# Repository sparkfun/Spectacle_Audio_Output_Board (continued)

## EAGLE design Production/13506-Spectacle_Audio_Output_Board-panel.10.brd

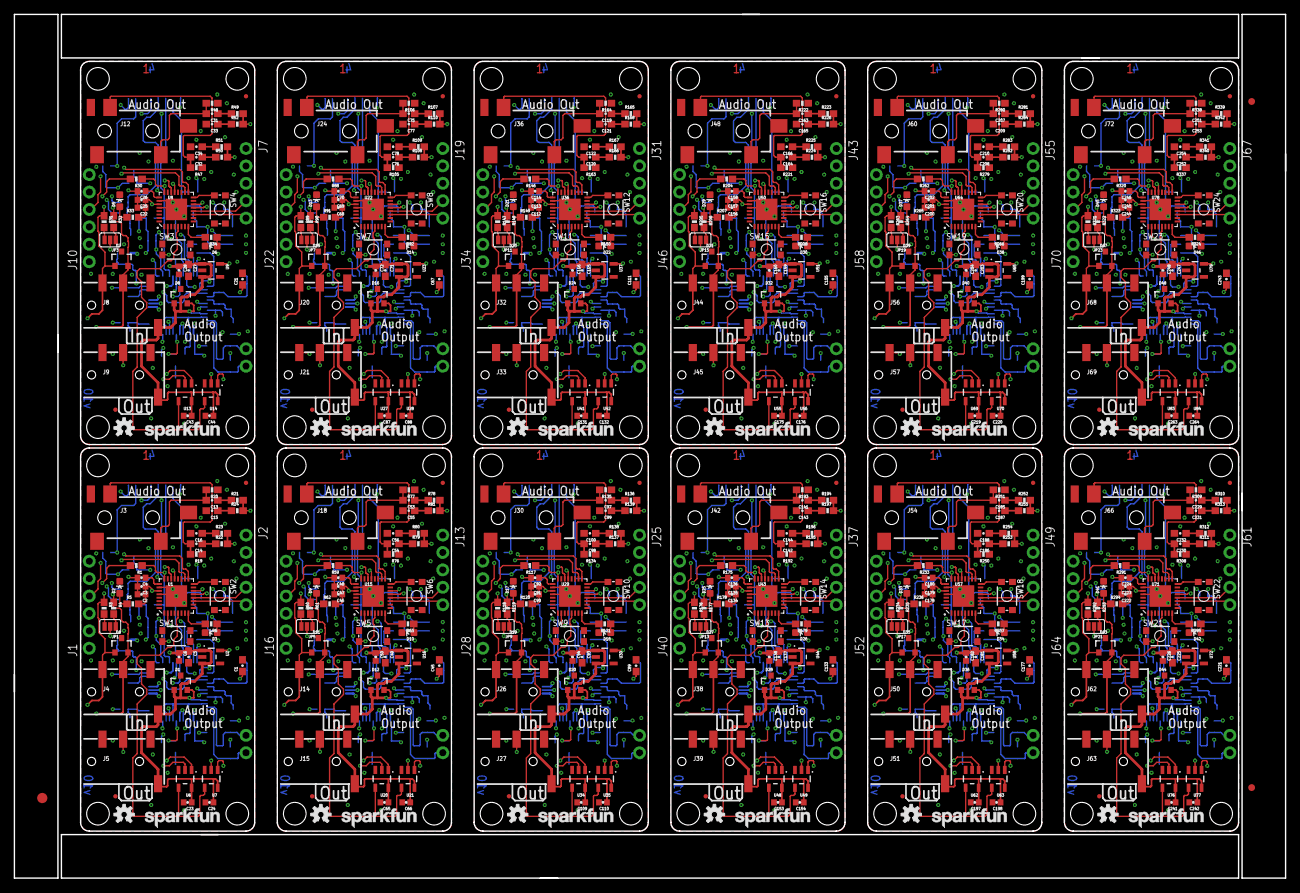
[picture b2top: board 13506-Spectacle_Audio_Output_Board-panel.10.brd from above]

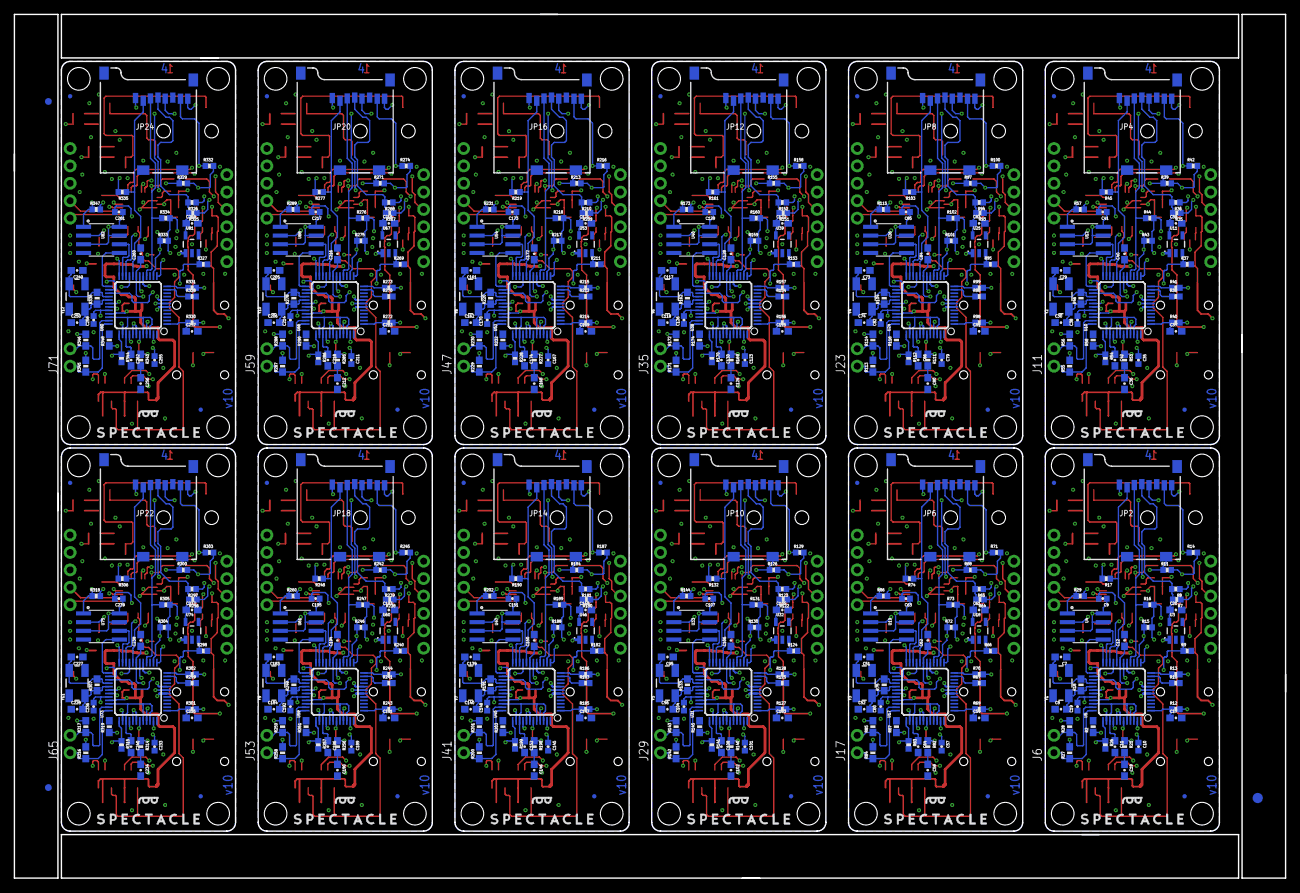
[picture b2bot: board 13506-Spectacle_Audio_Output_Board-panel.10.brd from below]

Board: 4 copper layers, 185.4 x 126.0 mm, 1002 parts (435 on the bottom side), 684 nets.

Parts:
C1, C5, C20, C21, C27, C39, C45, C49, C61, C67, C71, C83, C89, C93, C105, C111, C115, C127, C133, C137, C149, C155, C159, C171, C177, C181, C193, C199, C203, C215, C221, C225, C237, C243, C247, C259: 2.2uF; 0603-CAP
C2, C10, C19, C22, C35, C38, C46, C57, C60, C68, C79, C82, C90, C101, C104, C112, C123, C126, C134, C145, C148, C156, C167, C170, C178, C189, C192, C200, C211, C214, C222, C233, C236, C244, C255, C258: 1.0uF; 0402-CAP
C3, C4, C6, C9, C23, C24, C25, C26, C28, C41, C43, C44, C47, C48, C50, C63, C65, C66, C69, C70, C72, C85, C87, C88, C91, C92, C94, C107, C109, C110, C113, C114, C116, C129, C131, C132, C135, C136, C138, C151, C153, C154, C157, C158, C160, C173, C175, C176, C179, C180, C182, C195, C197, C198, C201, C202, C204, C217, C219, C220, C223, C224, C226, C239, C241, C242, C245, C246, C248, C261, C263, C264: 0.1uF; 0402-CAP
C7, C8, C29, C30, C51, C52, C73, C74, C95, C96, C117, C118, C139, C140, C161, C162, C183, C184, C205, C206, C227, C228, C249, C250: 22pF; 0603-CAP
C11, C12, C13, C14, C17, C31, C32, C37, C40, C42, C53, C54, C59, C62, C64, C75, C76, C81, C84, C86, C97, C98, C103, C106, C108, C119, C120, C125, C128, C130, C141, C142, C147, C150, C152, C163, C164, C169, C172, C174, C185, C186, C191, C194, C196, C207, C208, C213, C216, C218, C229, C230, C235, C238, C240, C251, C252, C257, C260, C262: 10uF; 0603-CAP
C15, C16, C33, C34, C55, C56, C77, C78, C99, C100, C121, C122, C143, C144, C165, C166, C187, C188, C209, C210, C231, C232, C253, C254: 10nF; 0603-CAP
C18, C36, C58, C80, C102, C124, C146, C168, C190, C212, C234, C256: 47nF; 0603-CAP
D1, D4, D7, D8, D11, D12, D15, D16, D19, D20, D23, D24, D27, D28, D31, D32, D35, D36, D39, D40, D43, D44, D47, D48: PESD1CAN; SOT23-3
D2, D3, D5, D6, D9, D10, D13, D14, D17, D18, D21, D22, D25, D26, D29, D30, D33, D34, D37, D38, D41, D42, D45, D46: RED; LED-0603
E$1, E$2: FIDUCIAL-1.5X3
E$3, E$4, E$7, E$8: FIDUCIAL-1X2
FD1, FD2, FD3, FD4, FD5, FD6, FD7, FD8, FD9, FD10, FD11, FD12, FD13, FD14, FD15, FD16, FD17, FD18, FD19, FD20, FD21, FD22, FD23, FD24, FD25, FD26, FD27, FD28, FD29, FD30, FD31, FD32, FD33, FD34, FD35, FD36, FD37, FD38, FD39, FD40, FD41, FD42, FD43, FD44, FD45, FD46, FD47, FD48: FIDUCIALUFIDUCIAL; MICRO-FIDUCIAL
H1, H2, H3, H4, H5, H6, H7, H8, H9, H10, H11, H12, H13, H14, H15, H16, H17, H18, H19, H20, H21, H22, H23, H24, H25, H26, H27, H28, H29, H30, H31, H32, H33, H34, H35, H36, H37, H38, H39, H40, H41, H42, H43, H44, H45, H46, H47, H48: STAND-OFF
J1, J10, J16, J22, J28, J34, J40, J46, J52, J58, J64, J70: 1X06_NO_SILK
J2, J7, J13, J19, J25, J31, J37, J43, J49, J55, J61, J67: 1X05_NO_SILK
J3, J12, J18, J24, J30, J36, J42, J48, J54, J60, J66, J72: AUDIO_JACK_3.5MM_SMD; AUDIO-JACK-3.5MM-SMD
J4, J5, J8, J9, J14, J15, J20, J21, J26, J27, J32, J33, J38, J39, J44, J45, J50, J51, J56, J57, J62, J63, J68, J69: AUDIO_JACK_TRRSSMD_RA; AUDIO_JACK_3.5MM_TRRS_SMD_RA
J6, J11, J17, J23, J29, J35, J41, J47, J53, J59, J65, J71: 1X02_NO_SILK
JP1, JP3, JP5, JP7, JP9, JP11, JP13, JP15, JP17, JP19, JP21, JP23: JUMPER-PAD-3-NC_BY_PASTE; PAD-JUMPER-3-NC_BY_PASTE_YES_SILK_FULL_BOX
JP2, JP4, JP6, JP8, JP10, JP12, JP14, JP16, JP18, JP20, JP22, JP24: USD-SOCKET; MICROSD_1:1
LOGO1, LOGO3, LOGO5, LOGO7, LOGO9, LOGO11, LOGO13, LOGO15, LOGO17, LOGO19, LOGO21, LOGO23: OSHW-LOGOS; OSHW-LOGO-S
LOGO2, LOGO4, LOGO6, LOGO8, LOGO10, LOGO12, LOGO14, LOGO16, LOGO18, LOGO20, LOGO22, LOGO24: SFE_LOGO_NAME.1_INCH; SFE_LOGO_NAME_.1
R1, R19, R20, R30, R47, R48, R59, R76, R77, R88, R105, R106, R117, R134, R135, R146, R163, R164, R175, R192, R193, R204, R221, R222, R233, R250, R251, R262, R279, R280, R291, R308, R309, R320, R337, R338: 10K; 0603-RES
R2, R18, R27, R28, R46, R55, R56, R58, R75, R84, R85, R87, R104, R113, R114, R116, R133, R142, R143, R145, R162, R171, R172, R174, R191, R200, R201, R203, R220, R229, R230, R232, R249, R258, R259, R261, R278, R287, R288, R290, R307, R316, R317, R319, R336, R345, R346, R348: 1M; 0603-RES
R3, R4, R31, R32, R60, R61, R89, R90, R118, R119, R147, R148, R176, R177, R205, R206, R234, R235, R263, R264, R292, R293, R321, R322: 4.7K; 0603-RES
R5, R6, R33, R34, R62, R63, R91, R92, R120, R121, R149, R150, R178, R179, R207, R208, R236, R237, R265, R266, R294, R295, R323, R324: 1K; 0603-RES
R7, R8, R9, R10, R11, R12, R13, R14, R15, R16, R17, R26, R29, R35, R36, R37, R38, R39, R40, R41, R42, R43, R44, R45, R54, R57, R64, R65, R66, R67, R68, R69, R70, R71, R72, R73, R74, R83, R86, R93, R94, R95, R96, R97, R98, R99, R100, R101, R102, R103, R112, R115, R122, R123, R124, R125, R126, R127, R128, R129, R130, R131, R132, R141, R144, R151, R152, R153, R154, R155, R156, R157, R158, R159, R160, R161, R170, R173, R180, R181, R182, R183, R184, R185, R186, R187, R188, R189, R190, R199, R202, R209, R210, R211, R212, R213, R214, R215, R216, R217, R218, R219, R228, R231, R238, R239, R240, R241, R242, R243, R244, R245, R246, R247, R248, R257, R260, R267, R268, R269, R270, R271, R272, R273, R274, R275, R276, R277, R286, R289, R296, R297, R298, R299, R300, R301, R302, R303, R304, R305, R306, R315, R318, R325, R326, R327, R328, R329, R330, R331, R332, R333, R334, R335, R344, R347: 100K; 0402-RES
R21, R22, R49, R50, R78, R79, R107, R108, R136, R137, R165, R166, R194, R195, R223, R224, R252, R253, R281, R282, R310, R311, R339, R340: 470; 0603-RES
R23, R24, R51, R52, R80, R81, R109, R110, R138, R139, R167, R168, R196, R197, R225, R226, R254, R255, R283, R284, R312, R313, R341, R342: 20; 0603-RES
R25, R53, R82, R111, R140, R169, R198, R227, R256, R285, R314, R343: 10; 0603-RES
SW1, SW2, SW3, SW4, SW5, SW6, SW7, SW8, SW9, SW10, SW11, SW12, SW13, SW14, SW15, SW16, SW17, SW18, SW19, SW20, SW21, SW22, SW23, SW24: TACTILE_SWITCH_SMD_4.6X2.8MM
U1, U8, U15, U22, U29, U36, U43, U50, U57, U64, U71, U78: CY8C4146LQI-S422; QFN-32
U2, U3, U9, U11, U16, U18, U23, U25, U30, U32, U37, U39, U44, U46, U51, U53, U58, U60, U65, U67, U72, U74, U79, U81: 3.3V; SOT23-5
U4, U12, U19, U26, U33, U40, U47, U54, U61, U68, U75, U82: AT25SF041-SOIC8; SO08
U5, U10, U17, U24, U31, U38, U45, U52, U59, U66, U73, U80: VS1000; LQFP-48
U6, U7, U13, U14, U20, U21, U27, U28, U34, U35, U41, U42, U48, U49, U55, U56, U62, U63, U69, U70, U76, U77, U83, U84: SN74LVC1G66; SOT23-5
Y1, Y2, Y3, Y4, Y5, Y6, Y7, Y8, Y9, Y10, Y11, Y12: 12MHz; CRYSTAL-SMD-5X3

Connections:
3.3V: C1.1, C2.1, C3.1, C9.1, J2.1, JP1.2, R1.2, R5.2, R27.2, R28.2, U1.27, U2.5, U4.3, U4.7, U4.8
3.3V1: C21.1, C22.1, C25.1, C41.1, J7.1, JP3.2, R30.2, R33.2, R55.2, R56.2, U8.27, U9.5, U12.3, U12.7, U12.8
3.3V2: C45.1, C46.1, C47.1, C63.1, J13.1, JP5.2, R59.2, R62.2, R84.2, R85.2, U15.27, U16.5, U19.3, U19.7, U19.8
3.3V3: C67.1, C68.1, C69.1, C85.1, J19.1, JP7.2, R88.2, R91.2, R113.2, R114.2, U22.27, U23.5, U26.3, U26.7, U26.8
3.3V4: C89.1, C90.1, C91.1, C107.1, J25.1, JP9.2, R117.2, R120.2, R142.2, R143.2, U29.27, U30.5, U33.3, U33.7, U33.8
3.3V5: C111.1, C112.1, C113.1, C129.1, J31.1, JP11.2, R146.2, R149.2, R171.2, R172.2, U36.27, U37.5, U40.3, U40.7, U40.8
3.3V6: C133.1, C134.1, C135.1, C151.1, J37.1, JP13.2, R175.2, R178.2, R200.2, R201.2, U43.27, U44.5, U47.3, U47.7, U47.8
3.3V7: C155.1, C156.1, C157.1, C173.1, J43.1, JP15.2, R204.2, R207.2, R229.2, R230.2, U50.27, U51.5, U54.3, U54.7, U54.8
3.3V8: C177.1, C178.1, C179.1, C195.1, J49.1, JP17.2, R233.2, R236.2, R258.2, R259.2, U57.27, U58.5, U61.3, U61.7, U61.8
3.3V9: C199.1, C200.1, C201.1, C217.1, J55.1, JP19.2, R262.2, R265.2, R287.2, R288.2, U64.27, U65.5, U68.3, U68.7, U68.8
3.3V10: C221.1, C222.1, C223.1, C239.1, J61.1, JP21.2, R291.2, R294.2, R316.2, R317.2, U71.27, U72.5, U75.3, U75.7, U75.8
3.3V11: C243.1, C244.1, C245.1, C261.1, J67.1, JP23.2, R320.2, R323.2, R345.2, R346.2, U78.27, U79.5, U82.3, U82.7, U82.8
BTN: SW2.1, U1.16
BTN1: SW4.1, U8.16
BTN2: SW6.1, U15.16
BTN3: SW8.1, U22.16
BTN4: SW10.1, U29.16
BTN5: SW12.1, U36.16
BTN6: SW14.1, U43.16
BTN7: SW16.1, U50.16
BTN8: SW18.1, U57.16
BTN9: SW20.1, U64.16
BTN10: SW22.1, U71.16
BTN11: SW24.1, U78.16
D1: R38.1, U10.11
D2: R41.1, U10.12
D3: R67.1, U17.11
D4: R70.1, U17.12
D5: R96.1, U24.11
D6: R10.1, U5.11
D7: R13.1, U5.12
D8: R99.1, U24.12
D9: R125.1, U31.11
D10: R128.1, U31.12
D11: R154.1, U38.11
D12: R157.1, U38.12
D13: R183.1, U45.11
D14: R186.1, U45.12
D15: R212.1, U52.11
D16: R215.1, U52.12
D17: R241.1, U59.11
D18: R244.1, U59.12
D19: R270.1, U66.11
D20: R273.1, U66.12
D21: R299.1, U73.11
D22: R302.1, U73.12
D23: R328.1, U80.11
D24: R331.1, U80.12
GBUF: R25.1, U5.43
GBUF1: R53.1, U10.43
GBUF2: R82.1, U17.43
GBUF3: R111.1, U24.43
GBUF4: R140.1, U31.43
GBUF5: R169.1, U38.43
GBUF6: R198.1, U45.43
GBUF7: R227.1, U52.43
GBUF8: R256.1, U59.43
GBUF9: R285.1, U66.43
GBUF10: R314.1, U73.43
GBUF11: R343.1, U80.43
GND: C1.2, C2.2, C3.2, C4.2, C5.2, C6.2, C7.1, C8.1, C9.2, C10.2, C11.2, C12.2, C15.2, C16.2, C17.2, C18.2, C19.1, C20.2, C23.2, C24.2, D1.3, D2.C, D3.C, D4.3, J1.1, J1.2, J2.2, J3.SLEEVE, J4.TIP, J5.TIP, JP2.6, JP2.CD2, JP2.GND1, JP2.GND3, R2.2, R9.2, R10.2, R19.1, R20.1, R26.2, SW1.3, SW2.3, U1.26, U1.28, U1.EP, U2.2, U3.2, U4.4, U5.6, U5.8, U5.18, U5.31, U5.38, U5.41, U5.42, U5.48, U6.3, U7.3
GND1: C21.2, C22.2, C25.2, C26.2, C27.2, C28.2, C29.1, C30.1, C33.2, C34.2, C35.2, C36.2, C37.2, C38.1, C39.2, C40.2, C41.2, C42.2, C43.2, C44.2, D5.C, D6.C, D7.3, D8.3, J7.2, J8.TIP, J9.TIP, J10.1, J10.2, J12.SLEEVE, JP4.6, JP4.CD2, JP4.GND1, JP4.GND3, R37.2, R38.2, R47.1, R48.1, R54.2, R58.2, SW3.3, SW4.3, U8.26, U8.28, U8.EP, U9.2, U10.6, U10.8, U10.18, U10.31, U10.38, U10.41, U10.42, U10.48, U11.2, U12.4, U13.3, U14.3
GND2: C45.2, C46.2, C47.2, C48.2, C49.2, C50.2, C51.1, C52.1, C55.2, C56.2, C57.2, C58.2, C59.2, C60.1, C61.2, C62.2, C63.2, C64.2, C65.2, C66.2, D9.C, D10.C, D11.3, D12.3, J13.2, J14.TIP, J15.TIP, J16.1, J16.2, J18.SLEEVE, JP6.6, JP6.CD2, JP6.GND1, JP6.GND3, R66.2, R67.2, R76.1, R77.1, R83.2, R87.2, SW5.3, SW6.3, U15.26, U15.28, U15.EP, U16.2, U17.6, U17.8, U17.18, U17.31, U17.38, U17.41, U17.42, U17.48, U18.2, U19.4, U20.3, U21.3
GND3: C67.2, C68.2, C69.2, C70.2, C71.2, C72.2, C73.1, C74.1, C77.2, C78.2, C79.2, C80.2, C81.2, C82.1, C83.2, C84.2, C85.2, C86.2, C87.2, C88.2, D13.C, D14.C, D15.3, D16.3, J19.2, J20.TIP, J21.TIP, J22.1, J22.2, J24.SLEEVE, JP8.6, JP8.CD2, JP8.GND1, JP8.GND3, R95.2, R96.2, R105.1, R106.1, R112.2, R116.2, SW7.3, SW8.3, U22.26, U22.28, U22.EP, U23.2, U24.6, U24.8, U24.18, U24.31, U24.38, U24.41, U24.42, U24.48, U25.2, U26.4, U27.3, U28.3
GND4: C89.2, C90.2, C91.2, C92.2, C93.2, C94.2, C95.1, C96.1, C99.2, C100.2, C101.2, C102.2, C103.2, C104.1, C105.2, C106.2, C107.2, C108.2, C109.2, C110.2, D17.C, D18.C, D19.3, D20.3, J25.2, J26.TIP, J27.TIP, J28.1, J28.2, J30.SLEEVE, JP10.6, JP10.CD2, JP10.GND1, JP10.GND3, R124.2, R125.2, R134.1, R135.1, R141.2, R145.2, SW9.3, SW10.3, U29.26, U29.28, U29.EP, U30.2, U31.6, U31.8, U31.18, U31.31, U31.38, U31.41, U31.42, U31.48, U32.2, U33.4, U34.3, U35.3
GND5: C111.2, C112.2, C113.2, C114.2, C115.2, C116.2, C117.1, C118.1, C121.2, C122.2, C123.2, C124.2, C125.2, C126.1, C127.2, C128.2, C129.2, C130.2, C131.2, C132.2, D21.C, D22.C, D23.3, D24.3, J31.2, J32.TIP, J33.TIP, J34.1, J34.2, J36.SLEEVE, JP12.6, JP12.CD2, JP12.GND1, JP12.GND3, R153.2, R154.2, R163.1, R164.1, R170.2, R174.2, SW11.3, SW12.3, U36.26, U36.28, U36.EP, U37.2, U38.6, U38.8, U38.18, U38.31, U38.38, U38.41, U38.42, U38.48, U39.2, U40.4, U41.3, U42.3
GND6: C133.2, C134.2, C135.2, C136.2, C137.2, C138.2, C139.1, C140.1, C143.2, C144.2, C145.2, C146.2, C147.2, C148.1, C149.2, C150.2, C151.2, C152.2, C153.2, C154.2, D25.C, D26.C, D27.3, D28.3, J37.2, J38.TIP, J39.TIP, J40.1, J40.2, J42.SLEEVE, JP14.6, JP14.CD2, JP14.GND1, JP14.GND3, R182.2, R183.2, R192.1, R193.1, R199.2, R203.2, SW13.3, SW14.3, U43.26, U43.28, U43.EP, U44.2, U45.6, U45.8, U45.18, U45.31, U45.38, U45.41, U45.42, U45.48, U46.2, U47.4, U48.3, U49.3
GND7: C155.2, C156.2, C157.2, C158.2, C159.2, C160.2, C161.1, C162.1, C165.2, C166.2, C167.2, C168.2, C169.2, C170.1, C171.2, C172.2, C173.2, C174.2, C175.2, C176.2, D29.C, D30.C, D31.3, D32.3, J43.2, J44.TIP, J45.TIP, J46.1, J46.2, J48.SLEEVE, JP16.6, JP16.CD2, JP16.GND1, JP16.GND3, R211.2, R212.2, R221.1, R222.1, R228.2, R232.2, SW15.3, SW16.3, U50.26, U50.28, U50.EP, U51.2, U52.6, U52.8, U52.18, U52.31, U52.38, U52.41, U52.42, U52.48, U53.2, U54.4, U55.3, U56.3
GND8: C177.2, C178.2, C179.2, C180.2, C181.2, C182.2, C183.1, C184.1, C187.2, C188.2, C189.2, C190.2, C191.2, C192.1, C193.2, C194.2, C195.2, C196.2, C197.2, C198.2, D33.C, D34.C, D35.3, D36.3, J49.2, J50.TIP, J51.TIP, J52.1, J52.2, J54.SLEEVE, JP18.6, JP18.CD2, JP18.GND1, JP18.GND3, R240.2, R241.2, R250.1, R251.1, R257.2, R261.2, SW17.3, SW18.3, U57.26, U57.28, U57.EP, U58.2, U59.6, U59.8, U59.18, U59.31, U59.38, U59.41, U59.42, U59.48, U60.2, U61.4, U62.3, U63.3
GND9: C199.2, C200.2, C201.2, C202.2, C203.2, C204.2, C205.1, C206.1, C209.2, C210.2, C211.2, C212.2, C213.2, C214.1, C215.2, C216.2, C217.2, C218.2, C219.2, C220.2, D37.C, D38.C, D39.3, D40.3, J55.2, J56.TIP, J57.TIP, J58.1, J58.2, J60.SLEEVE, JP20.6, JP20.CD2, JP20.GND1, JP20.GND3, R269.2, R270.2, R279.1, R280.1, R286.2, R290.2, SW19.3, SW20.3, U64.26, U64.28, U64.EP, U65.2, U66.6, U66.8, U66.18, U66.31, U66.38, U66.41, U66.42, U66.48, U67.2, U68.4, U69.3, U70.3
GND10: C221.2, C222.2, C223.2, C224.2, C225.2, C226.2, C227.1, C228.1, C231.2, C232.2, C233.2, C234.2, C235.2, C236.1, C237.2, C238.2, C239.2, C240.2, C241.2, C242.2, D41.C, D42.C, D43.3, D44.3, J61.2, J62.TIP, J63.TIP, J64.1, J64.2, J66.SLEEVE, JP22.6, JP22.CD2, JP22.GND1, JP22.GND3, R298.2, R299.2, R308.1, R309.1, R315.2, R319.2, SW21.3, SW22.3, U71.26, U71.28, U71.EP, U72.2, U73.6, U73.8, U73.18, U73.31, U73.38, U73.41, U73.42, U73.48, U74.2, U75.4, U76.3, U77.3
GND11: C243.2, C244.2, C245.2, C246.2, C247.2, C248.2, C249.1, C250.1, C253.2, C254.2, C255.2, C256.2, C257.2, C258.1, C259.2, C260.2, C261.2, C262.2, C263.2, C264.2, D45.C, D46.C, D47.3, D48.3, J67.2, J68.TIP, J69.TIP, J70.1, J70.2, J72.SLEEVE, JP24.6, JP24.CD2, JP24.GND1, JP24.GND3, R327.2, R328.2, R337.1, R338.1, R344.2, R348.2, SW23.3, SW24.3, U78.26, U78.28, U78.EP, U79.2, U80.6, U80.8, U80.18, U80.31, U80.38, U80.41, U80.42, U80.48, U81.2, U82.4, U83.3, U84.3
I2C_OUT_EN: U1.5, U6.4, U7.4
I2C_OUT_EN1: U8.5, U13.4, U14.4
I2C_OUT_EN2: U15.5, U20.4, U21.4
I2C_OUT_EN3: U22.5, U27.4, U28.4
I2C_OUT_EN4: U29.5, U34.4, U35.4
I2C_OUT_EN5: U36.5, U41.4, U42.4
I2C_OUT_EN6: U43.5, U48.4, U49.4
I2C_OUT_EN7: U50.5, U55.4, U56.4
I2C_OUT_EN8: U57.5, U62.4, U63.4
I2C_OUT_EN9: U64.5, U69.4, U70.4
I2C_OUT_EN10: U71.5, U76.4, U77.4
I2C_OUT_EN11: U78.5, U83.4, U84.4
LED: R6.2, U1.8
LED1: R34.2, U8.8
LED2: R63.2, U15.8
LED3: R92.2, U22.8
LED4: R121.2, U29.8
LED5: R150.2, U36.8
LED6: R179.2, U43.8
LED7: R208.2, U50.8
LED8: R237.2, U57.8
LED9: R266.2, U64.8
LED10: R295.2, U71.8
LED11: R324.2, U78.8
LEFT: R21.2, R24.2, U5.47
LEFT1: R49.2, R52.2, U10.47
LEFT2: R78.2, R81.2, U17.47
LEFT3: R107.2, R110.2, U24.47
LEFT4: R136.2, R139.2, U31.47
LEFT5: R165.2, R168.2, U38.47
LEFT6: R194.2, R197.2, U45.47
LEFT7: R223.2, R226.2, U52.47
LEFT8: R252.2, R255.2, U59.47
LEFT9: R281.2, R284.2, U66.47
LEFT10: R310.2, R313.2, U73.47
LEFT11: R339.2, R342.2, U80.47
L_AC: C13.2, J3.TIP, R20.2
L_AC1: C31.2, J12.TIP, R48.2
L_AC2: C53.2, J18.TIP, R77.2
L_AC3: C75.2, J24.TIP, R106.2
L_AC4: C97.2, J30.TIP, R135.2
L_AC5: C119.2, J36.TIP, R164.2
L_AC6: C141.2, J42.TIP, R193.2
L_AC7: C163.2, J48.TIP, R222.2
L_AC8: C185.2, J54.TIP, R251.2
L_AC9: C207.2, J60.TIP, R280.2
L_AC10: C229.2, J66.TIP, R309.2
L_AC11: C251.2, J72.TIP, R338.2
unnamed: JP2.1, R8.1
unnamed: JP1.3, R3.2
unnamed: JP3.3, R31.2
unnamed: D2.A, R5.1
unnamed: D3.A, R6.1
unnamed: JP1.1, R4.2
unnamed: JP2.8, R7.1
unnamed: C13.1, R21.1
unnamed: C15.1, R24.1
unnamed: C18.1, R25.2
unnamed: C10.1, U5.45
unnamed: C19.2, R2.1, U5.32
unnamed: JP3.1, R32.2
unnamed: D5.A, R33.1
unnamed: D6.A, R34.1
unnamed: JP4.1, R36.1
unnamed: C14.1, R22.1
unnamed: JP4.8, R35.1
unnamed: C31.1, R49.1
unnamed: C16.1, R23.1
unnamed: C33.1, R52.1
unnamed: C32.1, R50.1
unnamed: C34.1, R51.1
unnamed: C36.1, R53.2
unnamed: C35.1, U10.45
unnamed: C38.2, R58.1, U10.32
unnamed: JP5.3, R60.2
unnamed: JP5.1, R61.2
unnamed: D9.A, R62.1
unnamed: D10.A, R63.1
unnamed: JP6.1, R65.1
unnamed: JP6.8, R64.1
unnamed: C53.1, R78.1
unnamed: C55.1, R81.1
unnamed: C54.1, R79.1
unnamed: C56.1, R80.1
unnamed: C58.1, R82.2
unnamed: C57.1, U17.45
unnamed: C60.2, R87.1, U17.32
unnamed: JP7.3, R89.2
unnamed: JP7.1, R90.2
unnamed: D13.A, R91.1
unnamed: D14.A, R92.1
unnamed: JP8.1, R94.1
unnamed: JP8.8, R93.1
unnamed: C75.1, R107.1
unnamed: C77.1, R110.1
unnamed: C76.1, R108.1
unnamed: C78.1, R109.1
unnamed: C80.1, R111.2
unnamed: C79.1, U24.45
unnamed: C82.2, R116.1, U24.32
unnamed: JP9.3, R118.2
unnamed: JP9.1, R119.2
unnamed: D17.A, R120.1
unnamed: D18.A, R121.1
unnamed: JP10.1, R123.1
unnamed: JP10.8, R122.1
unnamed: C97.1, R136.1
unnamed: C99.1, R139.1
unnamed: C98.1, R137.1
unnamed: C100.1, R138.1
unnamed: C102.1, R140.2
unnamed: C101.1, U31.45
unnamed: C104.2, R145.1, U31.32
unnamed: JP11.3, R147.2
unnamed: JP11.1, R148.2
unnamed: D21.A, R149.1
unnamed: D22.A, R150.1
unnamed: JP12.1, R152.1
unnamed: JP12.8, R151.1
unnamed: C119.1, R165.1
unnamed: C121.1, R168.1
unnamed: C120.1, R166.1
unnamed: C122.1, R167.1
unnamed: C124.1, R169.2
unnamed: C123.1, U38.45
unnamed: C126.2, R174.1, U38.32
unnamed: JP13.3, R176.2
unnamed: JP13.1, R177.2
unnamed: D25.A, R178.1
unnamed: D26.A, R179.1
unnamed: JP14.1, R181.1
unnamed: JP14.8, R180.1
unnamed: C141.1, R194.1
unnamed: C143.1, R197.1
unnamed: C142.1, R195.1
unnamed: C144.1, R196.1
unnamed: C146.1, R198.2
unnamed: C145.1, U45.45
unnamed: C148.2, R203.1, U45.32
unnamed: JP15.3, R205.2
unnamed: JP15.1, R206.2
unnamed: D29.A, R207.1
unnamed: D30.A, R208.1
unnamed: JP16.1, R210.1
unnamed: JP16.8, R209.1
unnamed: C163.1, R223.1
unnamed: C165.1, R226.1
unnamed: C164.1, R224.1
unnamed: C166.1, R225.1
unnamed: C168.1, R227.2
unnamed: C167.1, U52.45
unnamed: C170.2, R232.1, U52.32
unnamed: JP17.3, R234.2
unnamed: JP17.1, R235.2
unnamed: D33.A, R236.1
unnamed: D34.A, R237.1
unnamed: JP18.1, R239.1
unnamed: JP18.8, R238.1
unnamed: C185.1, R252.1
unnamed: C187.1, R255.1
unnamed: C186.1, R253.1
unnamed: C188.1, R254.1
unnamed: C190.1, R256.2
unnamed: C189.1, U59.45
unnamed: C192.2, R261.1, U59.32
unnamed: JP19.3, R263.2
unnamed: JP19.1, R264.2
unnamed: D37.A, R265.1
unnamed: D38.A, R266.1
unnamed: JP20.1, R268.1
unnamed: JP20.8, R267.1
unnamed: C207.1, R281.1
unnamed: C209.1, R284.1
unnamed: C208.1, R282.1
unnamed: C210.1, R283.1
unnamed: C212.1, R285.2
unnamed: C211.1, U66.45
unnamed: C214.2, R290.1, U66.32
unnamed: JP21.3, R292.2
unnamed: JP21.1, R293.2
unnamed: D41.A, R294.1
unnamed: D42.A, R295.1
unnamed: JP22.1, R297.1
unnamed: JP22.8, R296.1
unnamed: C229.1, R310.1
unnamed: C231.1, R313.1
unnamed: C230.1, R311.1
unnamed: C232.1, R312.1
unnamed: C234.1, R314.2
unnamed: C233.1, U73.45
unnamed: C236.2, R319.1, U73.32
unnamed: JP23.3, R321.2
unnamed: JP23.1, R322.2
unnamed: D45.A, R323.1
unnamed: D46.A, R324.1
unnamed: JP24.1, R326.1
unnamed: JP24.8, R325.1
unnamed: C251.1, R339.1
unnamed: C253.1, R342.1
unnamed: C252.1, R340.1
unnamed: C254.1, R341.1
unnamed: C256.1, R343.2
unnamed: C255.1, U80.45
unnamed: C258.2, R348.1, U80.32
POWBTN: R26.1, U1.2, U5.37
POWBTN1: R54.1, U8.2, U10.37
POWBTN2: R83.1, U15.2, U17.37
POWBTN3: R112.1, U22.2, U24.37
POWBTN4: R141.1, U29.2, U31.37
POWBTN5: R170.1, U36.2, U38.37
POWBTN6: R199.1, U43.2, U45.37
POWBTN7: R228.1, U50.2, U52.37
POWBTN8: R257.1, U57.2, U59.37
POWBTN9: R286.1, U64.2, U66.37
POWBTN10: R315.1, U71.2, U73.37
POWBTN11: R344.1, U78.2, U80.37
RIGHT: R22.2, R23.2, U5.40
RIGHT1: R50.2, R51.2, U10.40
RIGHT2: R79.2, R80.2, U17.40
RIGHT3: R108.2, R109.2, U24.40
RIGHT4: R137.2, R138.2, U31.40
RIGHT5: R166.2, R167.2, U38.40
RIGHT6: R195.2, R196.2, U45.40
RIGHT7: R224.2, R225.2, U52.40
RIGHT8: R253.2, R254.2, U59.40
RIGHT9: R282.2, R283.2, U66.40
RIGHT10: R311.2, R312.2, U73.40
RIGHT11: R340.2, R341.2, U80.40
RXI: J1.4, U1.21
RXI1: J10.4, U8.21
RXI2: J16.4, U15.21
RXI3: J22.4, U22.21
RXI4: J28.4, U29.21
RXI5: J34.4, U36.21
RXI6: J40.4, U43.21
RXI7: J46.4, U50.21
RXI8: J52.4, U57.21
RXI9: J58.4, U64.21
RXI10: J64.4, U71.21
RXI11: J70.4, U78.21
R_AC: C14.2, J3.RING, R19.2
R_AC1: C32.2, J12.RING, R47.2
R_AC2: C54.2, J18.RING, R76.2
R_AC3: C76.2, J24.RING, R105.2
R_AC4: C98.2, J30.RING, R134.2
R_AC5: C120.2, J36.RING, R163.2
R_AC6: C142.2, J42.RING, R192.2
R_AC7: C164.2, J48.RING, R221.2
R_AC8: C186.2, J54.RING, R250.2
R_AC9: C208.2, J60.RING, R279.2
R_AC10: C230.2, J66.RING, R308.2
R_AC11: C252.2, J72.RING, R337.2
SCL: D4.1, J4.RING2, R3.1, U1.17, U6.1
SCL1: D7.1, J8.RING2, R31.1, U8.17, U13.1
SCL2: D11.1, J14.RING2, R60.1, U15.17, U20.1
SCL3: D15.1, J20.RING2, R89.1, U22.17, U27.1
SCL4: D19.1, J26.RING2, R118.1, U29.17, U34.1
SCL5: D23.1, J32.RING2, R147.1, U36.17, U41.1
SCL6: D27.1, J38.RING2, R176.1, U43.17, U48.1
SCL7: D31.1, J44.RING2, R205.1, U50.17, U55.1
SCL8: D35.1, J50.RING2, R234.1, U57.17, U62.1
SCL9: D39.1, J56.RING2, R263.1, U64.17, U69.1
SCL10: D43.1, J62.RING2, R292.1, U71.17, U76.1
SCL11: D47.1, J68.RING2, R321.1, U78.17, U83.1
SCLK: U4.6, U5.23
SCLK1: U10.23, U12.6
SCLK2: U17.23, U19.6
SCLK3: U24.23, U26.6
SCLK4: U31.23, U33.6
SCLK5: U38.23, U40.6
SCLK6: U45.23, U47.6
SCLK7: U52.23, U54.6
SCLK8: U59.23, U61.6
SCLK9: U66.23, U68.6
SCLK10: U73.23, U75.6
SCLK11: U80.23, U82.6
SCL_OUT: J5.RING2, U6.2
SCL_OUT1: J9.RING2, U13.2
SCL_OUT2: J15.RING2, U20.2
SCL_OUT3: J21.RING2, U27.2
SCL_OUT4: J27.RING2, U34.2
SCL_OUT5: J33.RING2, U41.2
SCL_OUT6: J39.RING2, U48.2
SCL_OUT7: J45.RING2, U55.2
SCL_OUT8: J51.RING2, U62.2
SCL_OUT9: J57.RING2, U69.2
SCL_OUT10: J63.RING2, U76.2
SCL_OUT11: J69.RING2, U83.2
SD3V1: R37.1, U10.17, U11.3
SD3V2: R66.1, U17.17, U18.3
SD3V3: R9.1, U3.3, U5.17
SD3V4: R95.1, U24.17, U25.3
SD3V5: R124.1, U31.17, U32.3
SD3V6: R153.1, U38.17, U39.3
SD3V7: R182.1, U45.17, U46.3
SD3V8: R211.1, U52.17, U53.3
SD3V9: R240.1, U59.17, U60.3
SD3V10: R269.1, U66.17, U67.3
SD3V11: R298.1, U73.17, U74.3
SD3V12: R327.1, U80.17, U81.3
SDA: D4.2, J4.RING1, R4.1, U1.18, U7.1
SDA1: D7.2, J8.RING1, R32.1, U8.18, U14.1
SDA2: D11.2, J14.RING1, R61.1, U15.18, U21.1
SDA3: D15.2, J20.RING1, R90.1, U22.18, U28.1
SDA4: D19.2, J26.RING1, R119.1, U29.18, U35.1
SDA5: D23.2, J32.RING1, R148.1, U36.18, U42.1
SDA6: D27.2, J38.RING1, R177.1, U43.18, U49.1
SDA7: D31.2, J44.RING1, R206.1, U50.18, U56.1
SDA8: D35.2, J50.RING1, R235.1, U57.18, U63.1
SDA9: D39.2, J56.RING1, R264.1, U64.18, U70.1
SDA10: D43.2, J62.RING1, R293.1, U71.18, U77.1
SDA11: D47.2, J68.RING1, R322.1, U78.18, U84.1
SDA_OUT: J5.RING1, U7.2
SDA_OUT1: J9.RING1, U14.2
SDA_OUT2: J15.RING1, U21.2
SDA_OUT3: J21.RING1, U28.2
SDA_OUT4: J27.RING1, U35.2
SDA_OUT5: J33.RING1, U42.2
SDA_OUT6: J39.RING1, U49.2
SDA_OUT7: J45.RING1, U56.2
SDA_OUT8: J51.RING1, U63.2
SDA_OUT9: J57.RING1, U70.2
SDA_OUT10: J63.RING1, U77.2
SDA_OUT11: J69.RING1, U84.2
SDCD: JP2.CD1, R11.1, U5.21
SDCD1: JP4.CD1, R39.1, U10.21
SDCD2: JP6.CD1, R68.1, U17.21
SDCD3: JP8.CD1, R97.1, U24.21
SDCD4: JP10.CD1, R126.1, U31.21
SDCD5: JP12.CD1, R155.1, U38.21
SDCD6: JP14.CD1, R184.1, U45.21
SDCD7: JP16.CD1, R213.1, U52.21
SDCD8: JP18.CD1, R242.1, U59.21
SDCD9: JP20.CD1, R271.1, U66.21
SDCD10: JP22.CD1, R300.1, U73.21
SDCD11: JP24.CD1, R329.1, U80.21
SDCK: JP2.5, R15.1, U5.14
SDCK1: JP4.5, R43.1, U10.14
SDCK2: JP6.5, R72.1, U17.14
SDCK3: JP8.5, R101.1, U24.14
SDCK4: JP10.5, R130.1, U31.14
SDCK5: JP12.5, R159.1, U38.14
SDCK6: JP14.5, R188.1, U45.14
SDCK7: JP16.5, R217.1, U52.14
SDCK8: JP18.5, R246.1, U59.14
SDCK9: JP20.5, R275.1, U66.14
SDCK10: JP22.5, R304.1, U73.14
SDCK11: JP24.5, R333.1, U80.14
SDDI: JP2.3, R16.1, U5.16
SDDI1: JP4.3, R44.1, U10.16
SDDI2: JP6.3, R73.1, U17.16
SDDI3: JP8.3, R102.1, U24.16
SDDI4: JP10.3, R131.1, U31.16
SDDI5: JP12.3, R160.1, U38.16
SDDI6: JP14.3, R189.1, U45.16
SDDI7: JP16.3, R218.1, U52.16
SDDI8: JP18.3, R247.1, U59.16
SDDI9: JP20.3, R276.1, U66.16
SDDI10: JP22.3, R305.1, U73.16
SDDI11: JP24.3, R334.1, U80.16
SDDO: JP2.7, R14.1, U5.13
SDDO1: JP4.7, R42.1, U10.13
SDDO2: JP6.7, R71.1, U17.13
SDDO3: JP8.7, R100.1, U24.13
SDDO4: JP10.7, R129.1, U31.13
SDDO5: JP12.7, R158.1, U38.13
SDDO6: JP14.7, R187.1, U45.13
SDDO7: JP16.7, R216.1, U52.13
SDDO8: JP18.7, R245.1, U59.13
SDDO9: JP20.7, R274.1, U66.13
SDDO10: JP22.7, R303.1, U73.13
SDDO11: JP24.7, R332.1, U80.13
SDXCS: JP2.2, R17.1, U5.20
SDXCS1: JP4.2, R45.1, U10.20
SDXCS2: JP6.2, R74.1, U17.20
SDXCS3: JP8.2, R103.1, U24.20
SDXCS4: JP10.2, R132.1, U31.20
SDXCS5: JP12.2, R161.1, U38.20
SDXCS6: JP14.2, R190.1, U45.20
SDXCS7: JP16.2, R219.1, U52.20
SDXCS8: JP18.2, R248.1, U59.20
SDXCS9: JP20.2, R277.1, U66.20
SDXCS10: JP22.2, R306.1, U73.20
SDXCS11: JP24.2, R335.1, U80.20
SI: U4.2, U5.24
SI1: U10.24, U12.2
SI2: U17.24, U19.2
SI3: U24.24, U26.2
SI4: U31.24, U33.2
SI5: U38.24, U40.2
SI6: U45.24, U47.2
SI7: U52.24, U54.2
SI8: U59.24, U61.2
SI9: U66.24, U68.2
SI10: U73.24, U75.2
SI11: U80.24, U82.2
SO: U4.5, U5.25
SO1: U10.25, U12.5
SO2: U17.25, U19.5
SO3: U24.25, U26.5
SO4: U31.25, U33.5
SO5: U38.25, U40.5
SO6: U45.25, U47.5
SO7: U52.25, U54.5
SO8: U59.25, U61.5
SO9: U66.25, U68.5
SO10: U73.25, U75.5
SO11: U80.25, U82.5
SWD_CLK: J2.4, U1.12
SWD_CLK1: J7.4, U8.12
SWD_CLK2: J13.4, U15.12
SWD_CLK3: J19.4, U22.12
SWD_CLK4: J25.4, U29.12
SWD_CLK5: J31.4, U36.12
SWD_CLK6: J37.4, U43.12
SWD_CLK7: J43.4, U50.12
SWD_CLK8: J49.4, U57.12
SWD_CLK9: J55.4, U64.12
SWD_CLK10: J61.4, U71.12
SWD_CLK11: J67.4, U78.12
SWD_DATA: J2.5, U1.11
SWD_DATA1: J7.5, U8.11
SWD_DATA2: J13.5, U15.11
SWD_DATA3: J19.5, U22.11
SWD_DATA4: J25.5, U29.11
SWD_DATA5: J31.5, U36.11
SWD_DATA6: J37.5, U43.11
SWD_DATA7: J43.5, U50.11
SWD_DATA8: J49.5, U57.11
SWD_DATA9: J55.5, U64.11
SWD_DATA10: J61.5, U71.11
SWD_DATA11: J67.5, U78.11
TXO: J1.5, U1.22
TXO1: J10.5, U8.22
TXO2: J16.5, U15.22
TXO3: J22.5, U22.22
TXO4: J28.5, U29.22
TXO5: J34.5, U36.22
TXO6: J40.5, U43.22
TXO7: J46.5, U50.22
TXO8: J52.5, U57.22
TXO9: J58.5, U64.22
TXO10: J64.5, U71.22
TXO11: J70.5, U78.22
USBN: J6.1, R27.1, U5.36
USBN1: J11.1, R55.1, U10.36
USBN2: J17.1, R84.1, U17.36
USBN3: J23.1, R113.1, U24.36
USBN4: J29.1, R142.1, U31.36
USBN5: J35.1, R171.1, U38.36
USBN6: J41.1, R200.1, U45.36
USBN7: J47.1, R229.1, U52.36
USBN8: J53.1, R258.1, U59.36
USBN9: J59.1, R287.1, U66.36
USBN10: J65.1, R316.1, U73.36
USBN11: J71.1, R345.1, U80.36
USBP: J6.2, R28.1, U5.35
USBP1: J11.2, R56.1, U10.35
USBP2: J17.2, R85.1, U17.35
USBP3: J23.2, R114.1, U24.35
USBP4: J29.2, R143.1, U31.35
USBP5: J35.2, R172.1, U38.35
USBP6: J41.2, R201.1, U45.35
USBP7: J47.2, R230.1, U52.35
USBP8: J53.2, R259.1, U59.35
USBP9: J59.2, R288.1, U66.35
USBP10: J65.2, R317.1, U73.35
USBP11: J71.2, R346.1, U80.35
VCC: C4.1, U1.25
VCC1: C26.1, U8.25
VCC2: C48.1, U15.25
VCC3: C70.1, U22.25
VCC4: C92.1, U29.25
VCC5: C114.1, U36.25
VCC6: C136.1, U43.25
VCC7: C158.1, U50.25
VCC8: C180.1, U57.25
VCC9: C202.1, U64.25
VCC10: C224.1, U71.25
VCC11: C246.1, U78.25
VCCIO: C12.1, R11.2, R12.2, R13.2, R14.2, R15.2, R16.2, R17.2, R29.2, U5.7, U5.19, U5.30
VCCIO1: C40.1, R39.2, R40.2, R41.2, R42.2, R43.2, R44.2, R45.2, R57.2, U10.7, U10.19, U10.30
VCCIO2: C62.1, R68.2, R69.2, R70.2, R71.2, R72.2, R73.2, R74.2, R86.2, U17.7, U17.19, U17.30
VCCIO3: C84.1, R97.2, R98.2, R99.2, R100.2, R101.2, R102.2, R103.2, R115.2, U24.7, U24.19, U24.30
VCCIO4: C106.1, R126.2, R127.2, R128.2, R129.2, R130.2, R131.2, R132.2, R144.2, U31.7, U31.19, U31.30
VCCIO5: C128.1, R155.2, R156.2, R157.2, R158.2, R159.2, R160.2, R161.2, R173.2, U38.7, U38.19, U38.30
VCCIO6: C150.1, R184.2, R185.2, R186.2, R187.2, R188.2, R189.2, R190.2, R202.2, U45.7, U45.19, U45.30
VCCIO7: C172.1, R213.2, R214.2, R215.2, R216.2, R217.2, R218.2, R219.2, R231.2, U52.7, U52.19, U52.30
VCCIO8: C194.1, R242.2, R243.2, R244.2, R245.2, R246.2, R247.2, R248.2, R260.2, U59.7, U59.19, U59.30
VCCIO9: C216.1, R271.2, R272.2, R273.2, R274.2, R275.2, R276.2, R277.2, R289.2, U66.7, U66.19, U66.30
VCCIO10: C238.1, R300.2, R301.2, R302.2, R303.2, R304.2, R305.2, R306.2, R318.2, U73.7, U73.19, U73.30
VCCIO11: C260.1, R329.2, R330.2, R331.2, R332.2, R333.2, R334.2, R335.2, R347.2, U80.7, U80.19, U80.30
VDD: C20.1, JP2.4, R7.2, R8.2, U3.5
VDD1: C39.1, JP4.4, R35.2, R36.2, U11.5
VDD2: C61.1, JP6.4, R64.2, R65.2, U18.5
VDD3: C83.1, JP8.4, R93.2, R94.2, U25.5
VDD4: C105.1, JP10.4, R122.2, R123.2, U32.5
VDD5: C127.1, JP12.4, R151.2, R152.2, U39.5
VDD6: C149.1, JP14.4, R180.2, R181.2, U46.5
VDD7: C171.1, JP16.4, R209.2, R210.2, U53.5
VDD8: C193.1, JP18.4, R238.2, R239.2, U60.5
VDD9: C215.1, JP20.4, R267.2, R268.2, U67.5
VDD10: C237.1, JP22.4, R296.2, R297.2, U74.5
VDD11: C259.1, JP24.4, R325.2, R326.2, U81.5
VDDA: C11.1, U5.34, U5.39, U5.44, U5.46
VDDA1: C42.1, U10.34, U10.39, U10.44, U10.46
VDDA2: C64.1, U17.34, U17.39, U17.44, U17.46
VDDA3: C86.1, U24.34, U24.39, U24.44, U24.46
VDDA4: C108.1, U31.34, U31.39, U31.44, U31.46
VDDA5: C130.1, U38.34, U38.39, U38.44, U38.46
VDDA6: C152.1, U45.34, U45.39, U45.44, U45.46
VDDA7: C174.1, U52.34, U52.39, U52.44, U52.46
VDDA8: C196.1, U59.34, U59.39, U59.44, U59.46
VDDA9: C218.1, U66.34, U66.39, U66.44, U66.46
VDDA10: C240.1, U73.34, U73.39, U73.44, U73.46
VDDA11: C262.1, U80.34, U80.39, U80.44, U80.46
VIN: C5.1, C6.1, C23.1, C24.1, D1.1, D1.2, J4.EARTH, J5.EARTH, U2.1, U2.3, U3.1, U5.33, U6.5, U7.5
VIN1: C27.1, C28.1, C43.1, C44.1, D8.1, D8.2, J8.EARTH, J9.EARTH, U9.1, U9.3, U10.33, U11.1, U13.5, U14.5
VIN2: C49.1, C50.1, C65.1, C66.1, D12.1, D12.2, J14.EARTH, J15.EARTH, U16.1, U16.3, U17.33, U18.1, U20.5, U21.5
VIN3: C71.1, C72.1, C87.1, C88.1, D16.1, D16.2, J20.EARTH, J21.EARTH, U23.1, U23.3, U24.33, U25.1, U27.5, U28.5
VIN4: C93.1, C94.1, C109.1, C110.1, D20.1, D20.2, J26.EARTH, J27.EARTH, U30.1, U30.3, U31.33, U32.1, U34.5, U35.5
VIN5: C115.1, C116.1, C131.1, C132.1, D24.1, D24.2, J32.EARTH, J33.EARTH, U37.1, U37.3, U38.33, U39.1, U41.5, U42.5
VIN6: C137.1, C138.1, C153.1, C154.1, D28.1, D28.2, J38.EARTH, J39.EARTH, U44.1, U44.3, U45.33, U46.1, U48.5, U49.5
VIN7: C159.1, C160.1, C175.1, C176.1, D32.1, D32.2, J44.EARTH, J45.EARTH, U51.1, U51.3, U52.33, U53.1, U55.5, U56.5
VIN8: C181.1, C182.1, C197.1, C198.1, D36.1, D36.2, J50.EARTH, J51.EARTH, U58.1, U58.3, U59.33, U60.1, U62.5, U63.5
VIN9: C203.1, C204.1, C219.1, C220.1, D40.1, D40.2, J56.EARTH, J57.EARTH, U65.1, U65.3, U66.33, U67.1, U69.5, U70.5
VIN10: C225.1, C226.1, C241.1, C242.1, D44.1, D44.2, J62.EARTH, J63.EARTH, U72.1, U72.3, U73.33, U74.1, U76.5, U77.5
VIN11: C247.1, C248.1, C263.1, C264.1, D48.1, D48.2, J68.EARTH, J69.EARTH, U79.1, U79.3, U80.33, U81.1, U83.5, U84.5
VS_RX: U1.14, U5.27
VS_RX1: U8.14, U10.27
VS_RX2: U15.14, U17.27
VS_RX3: U22.14, U24.27
VS_RX4: U29.14, U31.27
VS_RX5: U36.14, U38.27
VS_RX6: U43.14, U45.27
VS_RX7: U50.14, U52.27
VS_RX8: U57.14, U59.27
VS_RX9: U64.14, U66.27
VS_RX10: U71.14, U73.27
VS_RX11: U78.14, U80.27
VS_TX: U1.13, U5.26
VS_TX1: U8.13, U10.26
VS_TX2: U15.13, U17.26
VS_TX3: U22.13, U24.26
VS_TX4: U29.13, U31.26
VS_TX5: U36.13, U38.26
VS_TX6: U43.13, U45.26
VS_TX7: U50.13, U52.26
VS_TX8: U57.13, U59.26
VS_TX9: U64.13, U66.26
VS_TX10: U71.13, U73.26
VS_TX11: U78.13, U80.26
XCS: R29.1, U4.1, U5.22
XCS1: R57.1, U10.22, U12.1
XCS2: R86.1, U17.22, U19.1
XCS3: R115.1, U24.22, U26.1
XCS4: R144.1, U31.22, U33.1
XCS5: R173.1, U38.22, U40.1
XCS6: R202.1, U45.22, U47.1
XCS7: R231.1, U52.22, U54.1
XCS8: R260.1, U59.22, U61.1
XCS9: R289.1, U66.22, U68.1
XCS10: R318.1, U73.22, U75.1
XCS11: R347.1, U80.22, U82.1
XRES: J2.3, R1.1, SW1.1, U1.24
XRES1: J7.3, R30.1, SW3.1, U8.24
XRES2: J13.3, R59.1, SW5.1, U15.24
XRES3: J19.3, R88.1, SW7.1, U22.24
XRES4: J25.3, R117.1, SW9.1, U29.24
XRES5: J31.3, R146.1, SW11.1, U36.24
XRES6: J37.3, R175.1, SW13.1, U43.24
XRES7: J43.3, R204.1, SW15.1, U50.24
XRES8: J49.3, R233.1, SW17.1, U57.24
XRES9: J55.3, R262.1, SW19.1, U64.24
XRES10: J61.3, R291.1, SW21.1, U71.24
XRES11: J67.3, R320.1, SW23.1, U78.24
XRST: C17.1, R12.1, U5.1
XRST1: C37.1, R40.1, U10.1
XRST2: C59.1, R69.1, U17.1
XRST3: C81.1, R98.1, U24.1
XRST4: C103.1, R127.1, U31.1
XRST5: C125.1, R156.1, U38.1
XRST6: C147.1, R185.1, U45.1
XRST7: C169.1, R214.1, U52.1
XRST8: C191.1, R243.1, U59.1
XRST9: C213.1, R272.1, U66.1
XRST10: C235.1, R301.1, U73.1
XRST11: C257.1, R330.1, U80.1
XTAL0: C8.2, R18.1, U5.29, Y1.1
XTAL1: C7.2, R18.2, U5.28, Y1.3
XTAL2: C30.2, R46.1, U10.29, Y2.1
XTAL3: C29.2, R46.2, U10.28, Y2.3
XTAL4: C52.2, R75.1, U17.29, Y3.1
XTAL5: C51.2, R75.2, U17.28, Y3.3
XTAL6: C74.2, R104.1, U24.29, Y4.1
XTAL7: C73.2, R104.2, U24.28, Y4.3
XTAL8: C96.2, R133.1, U31.29, Y5.1
XTAL9: C95.2, R133.2, U31.28, Y5.3
XTAL10: C118.2, R162.1, U38.29, Y6.1
XTAL11: C117.2, R162.2, U38.28, Y6.3
XTAL12: C140.2, R191.1, U45.29, Y7.1
XTAL13: C139.2, R191.2, U45.28, Y7.3
XTAL14: C162.2, R220.1, U52.29, Y8.1
XTAL15: C161.2, R220.2, U52.28, Y8.3
XTAL16: C184.2, R249.1, U59.29, Y9.1
XTAL17: C183.2, R249.2, U59.28, Y9.3
XTAL18: C206.2, R278.1, U66.29, Y10.1
XTAL19: C205.2, R278.2, U66.28, Y10.3
XTAL20: C228.2, R307.1, U73.29, Y11.1
XTAL21: C227.2, R307.2, U73.28, Y11.3
XTAL22: C250.2, R336.1, U80.29, Y12.1
XTAL23: C249.2, R336.2, U80.28, Y12.3

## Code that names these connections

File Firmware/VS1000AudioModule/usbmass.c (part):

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    */
    PERIP(GPIO1_DDR)   |=  1;
    PERIP(GPIO1_MODE)  &= ~1;
    PERIP(GPIO1_CLEAR_MASK) = 1; /*XCS down, possibly consumes IO power*/
    /*
      You may also need to draw IOVDD empty through RX pull-up
     */
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      );

#if 0  
  PERIP(GPIO1_ODATA) |=  LED1|LED2;
  PERIP(GPIO1_DDR)   |=  LED1|LED2;
  PERIP(GPIO1_MODE)  &= ~(LED1|LED2);
#endif

  player.volumeOffset = 0;
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
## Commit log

2016-08-29 Remove firmware cruft
2016-09-08 Submitted for review by QC
2016-09-09 Fixes from QC review
2016-10-11 Added downstream power control circuitry
2016-10-31 Change pullup resistor values to 4.7k Add firmware to repo
2016-10-31 Changes from review/checklist
2016-11-01 Fixes from review
2016-11-02 Flipped board to right side up
2016-11-29 Working checkpoint - Behavior configuration over I2C works - Reading triggers over I2C works - Changing I2C address does NOT work
2016-12-20 Firmware commit All functionality present and passes initial test
2017-01-12 Update sch and brd to V10
2017-01-23 Touch ups before v10 double check
2017-01-24 Cleaned up files for release. - Removed debug files - Removed some debugging statements that had been commented - Added headers to all files
2017-01-25 Reduced data needed to program board
2017-02-02 Moved some text on schematic for clarity
2017-02-09 panel
2017-04-05 Change baud rate to 9600
